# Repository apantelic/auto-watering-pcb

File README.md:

#  Automatic Plant Watering System - PCB Project

This is a simple PCB project for an automatic plant watering system using an Arduino Nano.
It monitors temperature and humidity, tracks time with a real-time clock (RTC), and controls a water pump via a relay.
The system includes an LCD for displaying data and a push button for manual pump activation.

## Overview
This project is a custom PCB for an automated plant watering system. It integrates an RTC module, temperature/humidity sensor, relay for pump control, and an LCD for displaying status.

While this version does not include soil moisture sensing, it can be manually activated using a button and is fully extendable for automatic operation in the future.

##  Components

- Arduino Nano
- DHT11 sensor (temperature and humidity)
- DS1302 Real Time Clock (RTC) module
- HL-525 Relay module (controls water pump)
- 16x2 LCD display with I2C
- Push button (manual pump activation)
- LED indicator (pump status)
- Resistors: 10kΩ (pull-up), 330Ω (LED current limiting)
- 2-pin screw terminal (pump connector)
- 3-pin headers (for DHT11, RTC, and other I/O connections)

##  Schematic & PCB

[KiCAD 8](https://www.kicad.org/)

### Sensors & Modules

- DS18B20 Temperature Sensor (digital, 3-pin)
- HL-52S Relay Module
- DS1302 Real Time Clock (RTC) module

## Author

Anđela Pantelić, student of Electrical Engineering 2025.

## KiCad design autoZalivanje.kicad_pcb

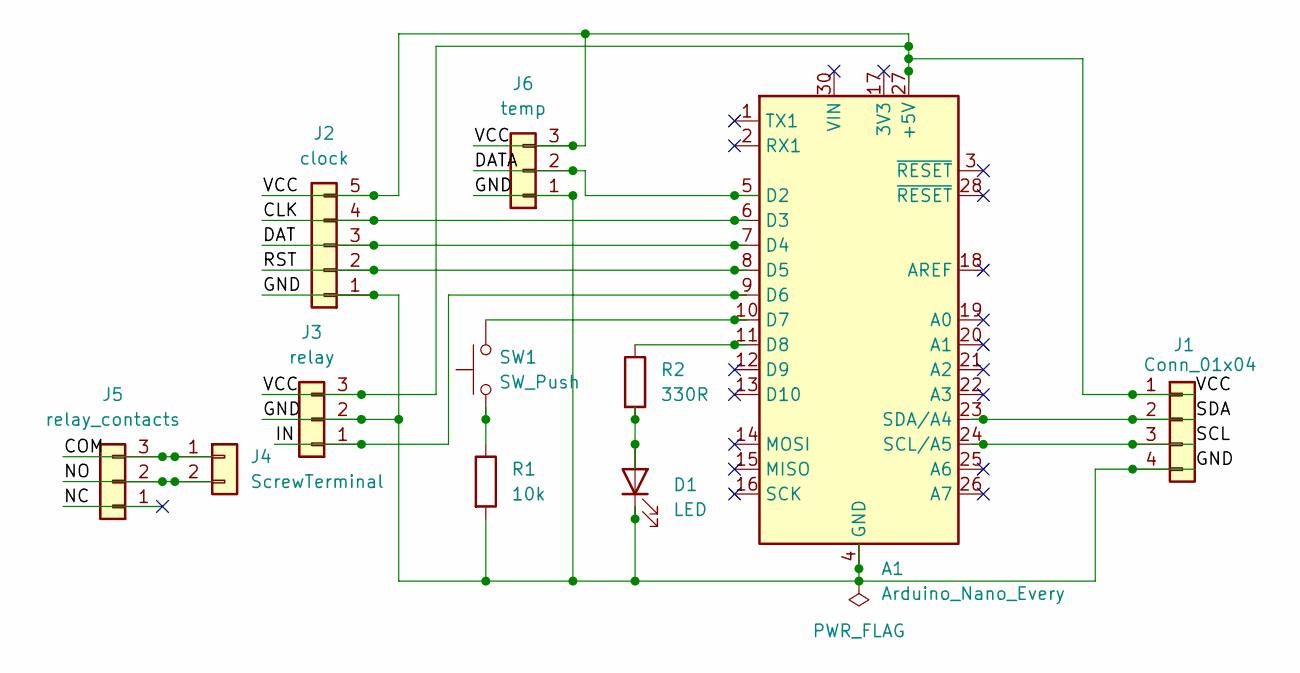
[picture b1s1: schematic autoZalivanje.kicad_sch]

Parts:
A1: Arduino_Nano_Every; Arduino_Nano
D1: LED; LED_D5.0mm
J1: Conn_01x04; PinHeader_1x04_P2.54mm_Vertical
J2: clock; PinHeader_1x05_P2.54mm_Vertical
J3: relay; PinHeader_1x03_P2.54mm_Vertical
J4: ScrewTerminal; PinHeader_1x02_P2.54mm_Vertical
J5: relay_contacts; PinHeader_1x03_P2.54mm_Vertical
J6: temp; PinHeader_1x03_P2.54mm_Vertical
R1: 10k; R_Axial_DIN0309_L9.0mm_D3.2mm_P2.54mm_Vertical
R2: 330R; R_Axial_DIN0309_L9.0mm_D3.2mm_P2.54mm_Vertical
SW1: SW_Push; SW_PUSH_6mm

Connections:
/CLK: A1.6 (D3), J2.4
/COM: J4.1, J5.3
/DAT: A1.7 (D4), J2.3
/DATA: A1.5 (D2), J6.2
/GND: A1.4 (GND), A1.29 (GND), D1.1 (K), J1.4, J2.1, J3.2, J6.1, R1.2
/IN: A1.9 (D6), J3.1
/NC: J5.1
/NO: J4.2, J5.2
/RST: A1.8 (D5), J2.2
/SCL: A1.24 (SCL/A5), J1.3
/SDA: A1.23 (SDA/A4), J1.2
/VCC: A1.27 (+5V), J1.1, J2.5, J3.3, J6.3
unnamed: A1.10 (D7), SW1.2
unnamed: A1.11 (D8), R2.1
unnamed: D1.2 (A), R2.2
unnamed: R1.1, SW1.1

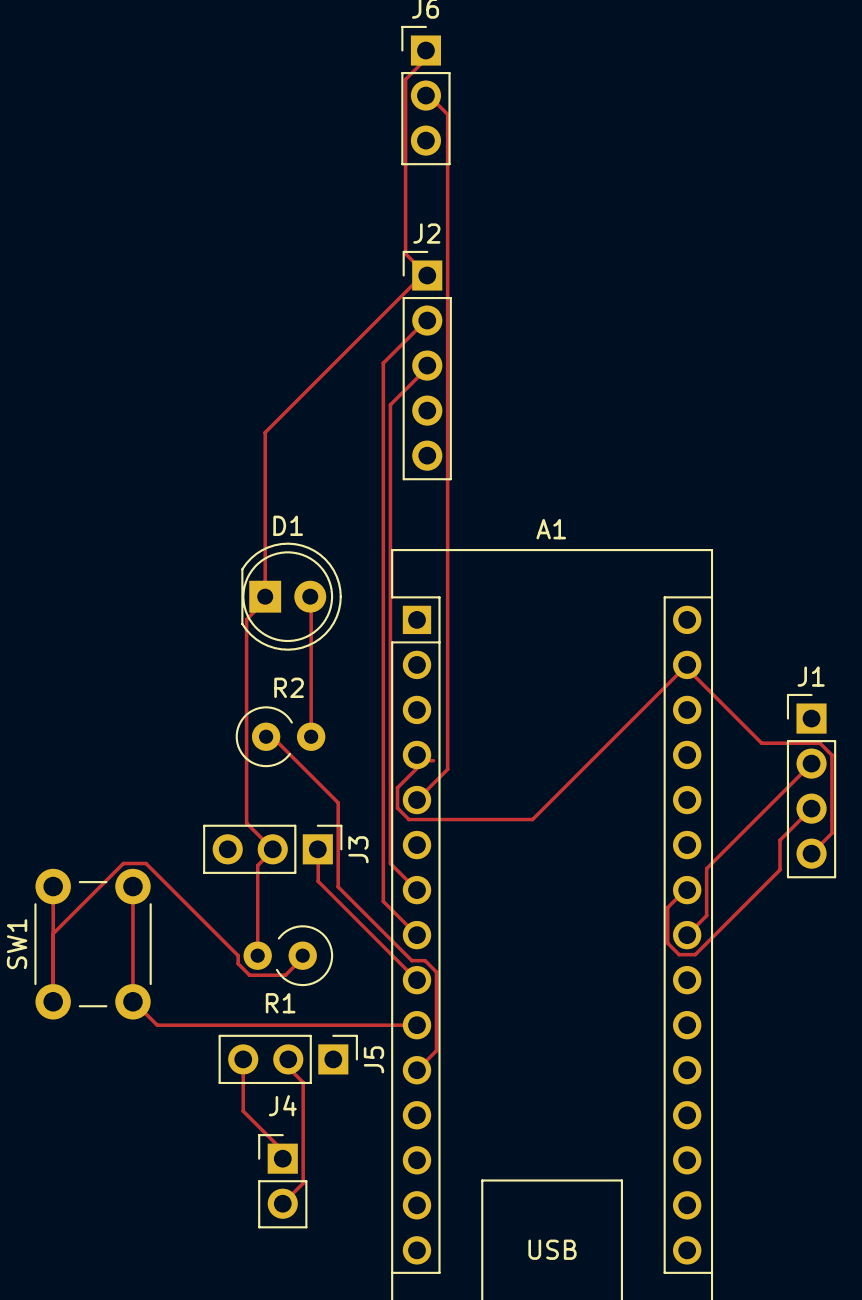
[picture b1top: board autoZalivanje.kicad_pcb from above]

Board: 2 copper layers, 11 parts (0 on the bottom side), 15 nets.
